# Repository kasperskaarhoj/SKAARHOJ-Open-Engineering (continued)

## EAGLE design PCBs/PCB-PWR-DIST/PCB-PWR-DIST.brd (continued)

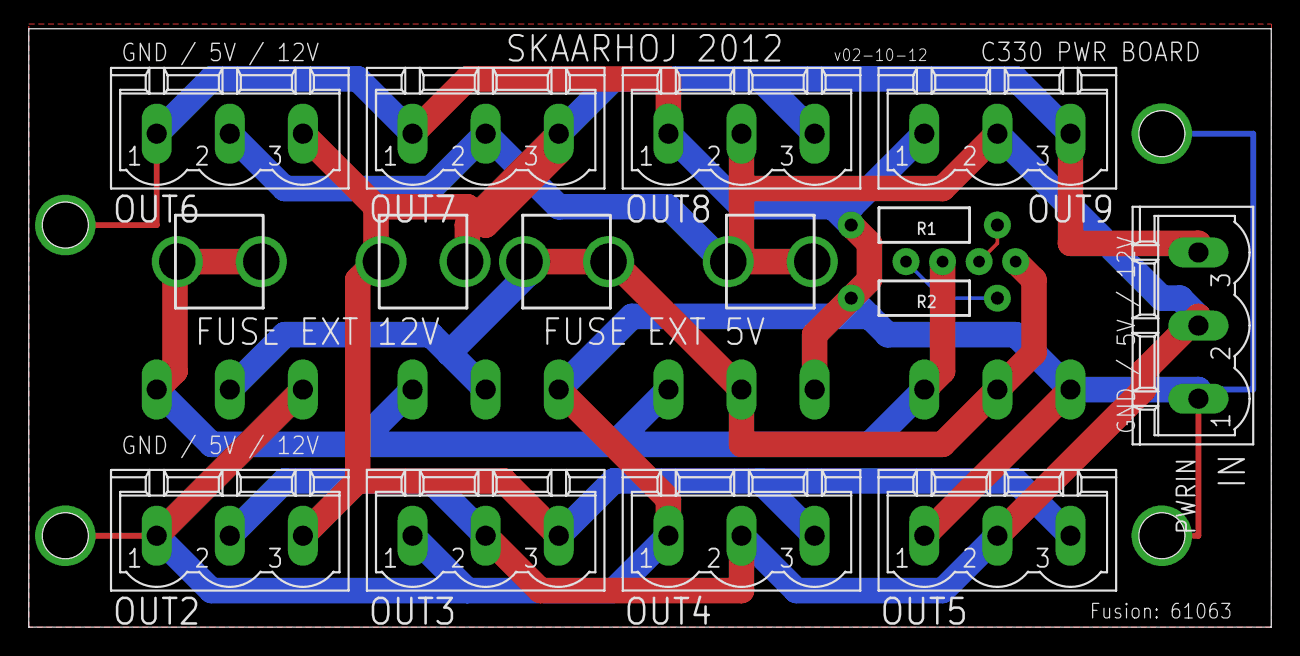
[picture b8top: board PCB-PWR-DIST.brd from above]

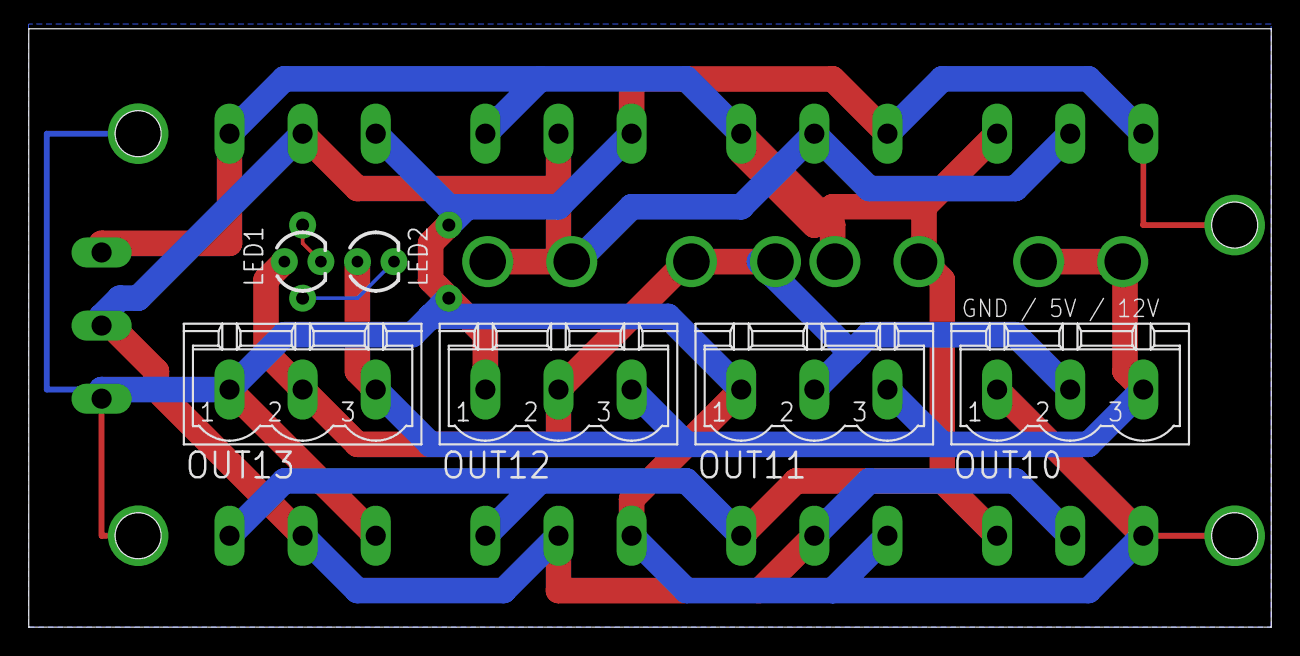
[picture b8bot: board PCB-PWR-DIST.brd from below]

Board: 2 copper layers, 86.3 x 41.6 mm, 19 parts (6 on the bottom side), 7 nets.
